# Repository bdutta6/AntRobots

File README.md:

# ant-robots

##Contributors

Initial Author: Vadim Linevich
Email: vadim.linevich@gmail.com

Modified by: Jungsoo Park
Email : ryanryan0906@hotmail.com

Modified by: Bahnisikha Dutta
Email : bahnisikha3474@gmail.com

Modified by: Ross Warkentin
Email: ross.warkentin@gmail.com

[Guide to .md files](https://guides.github.com/features/mastering-markdown/)

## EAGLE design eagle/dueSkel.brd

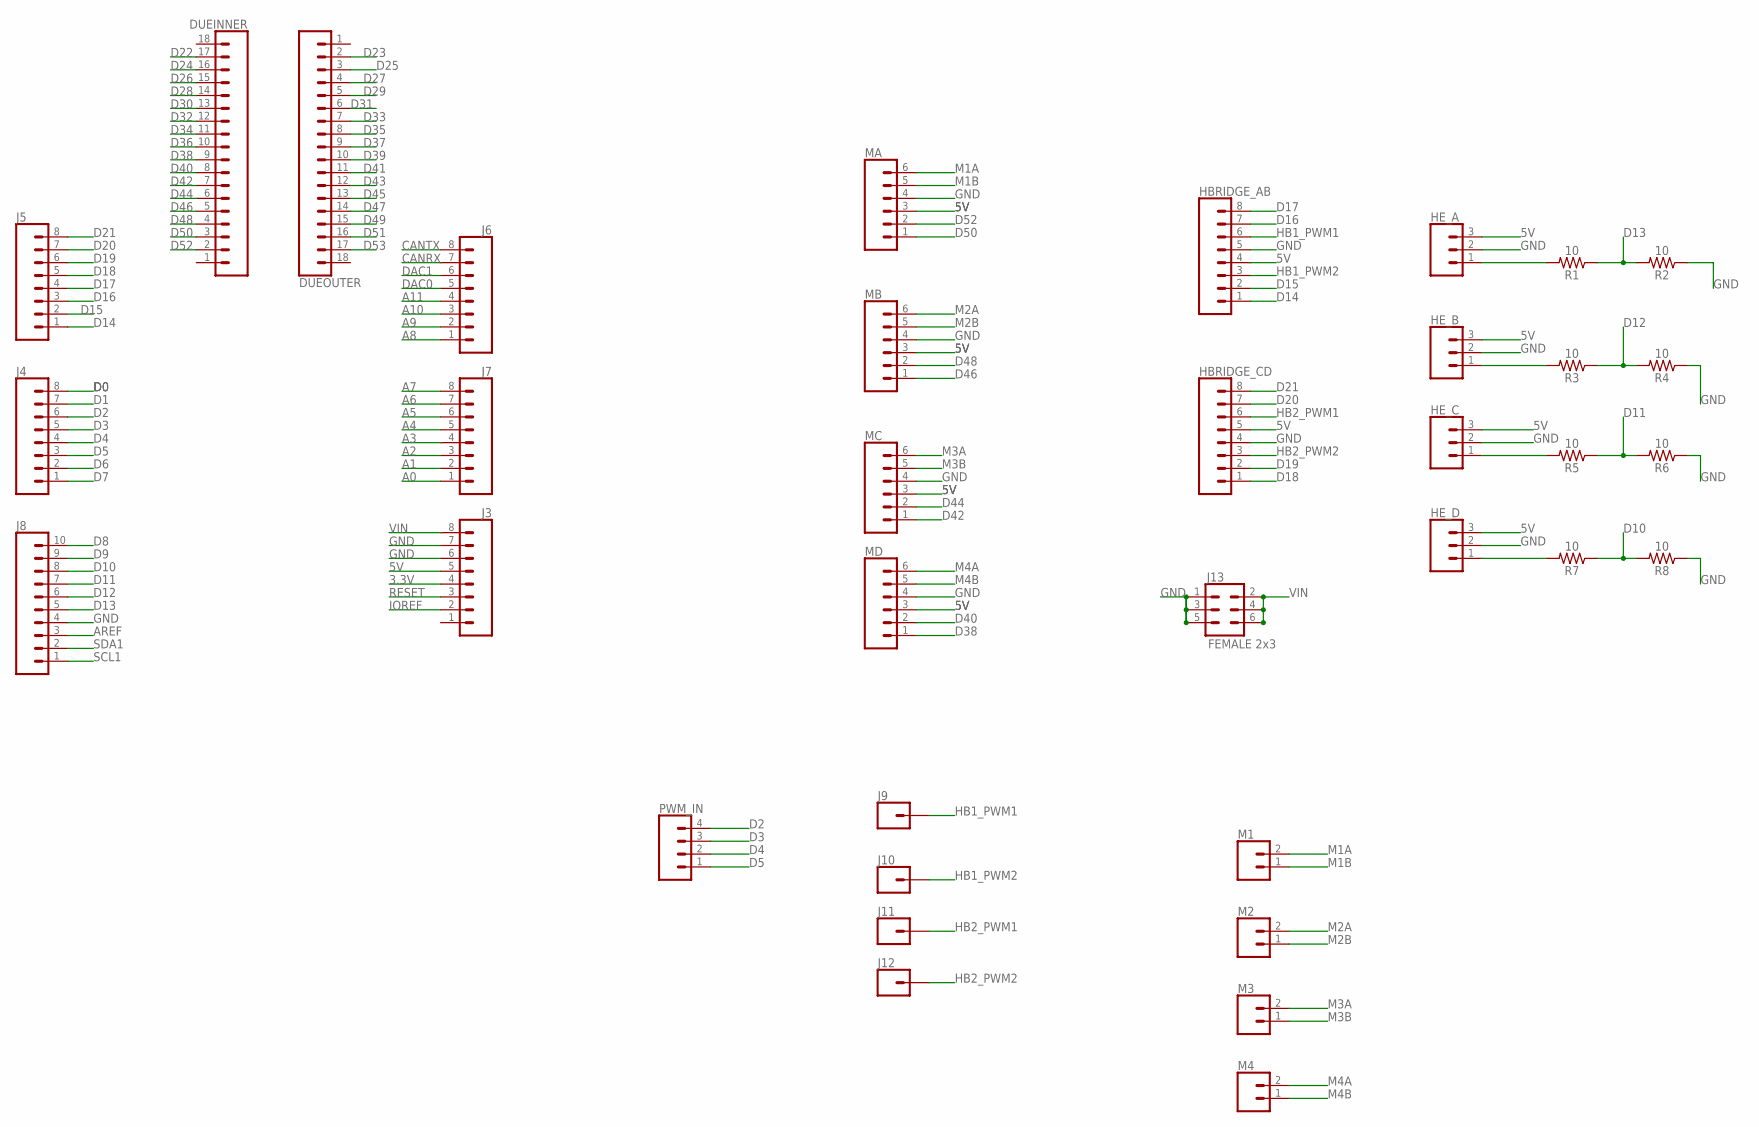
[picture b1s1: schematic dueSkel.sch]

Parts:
DUEINNER: CONN_18; 1X18
DUEOUTER: CONN_18; 1X18
HBRIDGE_AB: CONN_08"; 1X08
HBRIDGE_CD: CONN_08"; 1X08
HE_A: CONN_03; 1X03
HE_B: CONN_03; 1X03
HE_C: CONN_03; 1X03
HE_D: CONN_03; 1X03
J3, J4, J5, J6, J7: CONN_08"; 1X08
J8: CONN_10"; 1X10
J9, J10, J11, J12: CONN_01; 1X01
J13: FEMALE 2x3; 2X3
M1, M2, M3, M4: CONN_02; 1X02
MA: CONN_06SILK_FEMALE_PTH; 1X06
MB: CONN_06SILK_FEMALE_PTH; 1X06
MC: CONN_06SILK_FEMALE_PTH; 1X06
MD: CONN_06SILK_FEMALE_PTH; 1X06
PWM_IN: CONN_04; 1X04
R1, R2, R3, R4, R5, R6, R7, R8: 10; AXIAL-0.3

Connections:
3.3V: J3.4
5V: HBRIDGE_AB.4, HBRIDGE_CD.5, HE_A.3, HE_B.3, HE_C.3, HE_D.3, J3.5, MA.3, MB.3, MC.3, MD.3
A0: J7.1
A1: J7.2
A2: J7.3
A3: J7.4
A4: J7.5
A5: J7.6
A6: J7.7
A7: J7.8
A8: J6.1
A9: J6.2
A10: J6.3
A11: J6.4
AREF: J8.3
CANRX: J6.7
CANTX: J6.8
D0: J4.8
D1: J4.7
D2: J4.6, PWM_IN.4
D3: J4.5, PWM_IN.3
D4: J4.4, PWM_IN.2
D5: J4.3, PWM_IN.1
D6: J4.2
D7: J4.1
D8: J8.10
D9: J8.9
D10: J8.8, R7.P$1 (1), R8.P$2 (2)
D11: J8.7, R5.P$1 (1), R6.P$2 (2)
D12: J8.6, R3.P$1 (1), R4.P$2 (2)
D13: J8.5, R1.P$1 (1), R2.P$2 (2)
D14: HBRIDGE_AB.1, J5.1
D15: HBRIDGE_AB.2, J5.2
D16: HBRIDGE_AB.7, J5.3
D17: HBRIDGE_AB.8, J5.4
D18: HBRIDGE_CD.1, J5.5
D19: HBRIDGE_CD.2, J5.6
D20: HBRIDGE_CD.7, J5.7
D21: HBRIDGE_CD.8, J5.8
D22: DUEINNER.17
D23: DUEOUTER.2
D24: DUEINNER.16
D25: DUEOUTER.3
D26: DUEINNER.15
D27: DUEOUTER.4
D28: DUEINNER.14
D29: DUEOUTER.5
D30: DUEINNER.13
D31: DUEOUTER.6
D32: DUEINNER.12
D33: DUEOUTER.7
D34: DUEINNER.11
D35: DUEOUTER.8
D36: DUEINNER.10
D37: DUEOUTER.9
D38: DUEINNER.9, MD.1
D39: DUEOUTER.10
D40: DUEINNER.8, MD.2
D41: DUEOUTER.11
D42: DUEINNER.7, MC.1
D43: DUEOUTER.12
D44: DUEINNER.6, MC.2
D45: DUEOUTER.13
D46: DUEINNER.5, MB.1
D47: DUEOUTER.14
D48: DUEINNER.4, MB.2
D49: DUEOUTER.15
D50: DUEINNER.3, MA.1
D51: DUEOUTER.16
D52: DUEINNER.2, MA.2
D53: DUEOUTER.17
DAC0: J6.5
DAC1: J6.6
GND: HBRIDGE_AB.5, HBRIDGE_CD.4, HE_A.2, HE_B.2, HE_C.2, HE_D.2, J3.6, J3.7, J8.4, J13.1, J13.3, J13.5, MA.4, MB.4, MC.4, MD.4, R2.P$1 (1), R4.P$1 (1), R6.P$1 (1), R8.P$1 (1)
HB1_PWM1: HBRIDGE_AB.6, J9.1
HB1_PWM2: HBRIDGE_AB.3, J10.1
HB2_PWM1: HBRIDGE_CD.6, J11.1
HB2_PWM2: HBRIDGE_CD.3, J12.1
IOREF: J3.2
M1A: M1.2, MA.6
M1B: M1.1, MA.5
M2A: M2.2, MB.6
M2B: M2.1, MB.5
M3A: M3.2, MC.6
M3B: M3.1, MC.5
M4A: M4.2, MD.6
M4B: M4.1, MD.5
unnamed: HE_A.1, R1.P$2 (2)
unnamed: HE_B.1, R3.P$2 (2)
unnamed: HE_C.1, R5.P$2 (2)
unnamed: HE_D.1, R7.P$2 (2)
RESET: J3.3
SCL1: J8.1
SDA1: J8.2
VIN: J3.8, J13.2, J13.4, J13.6

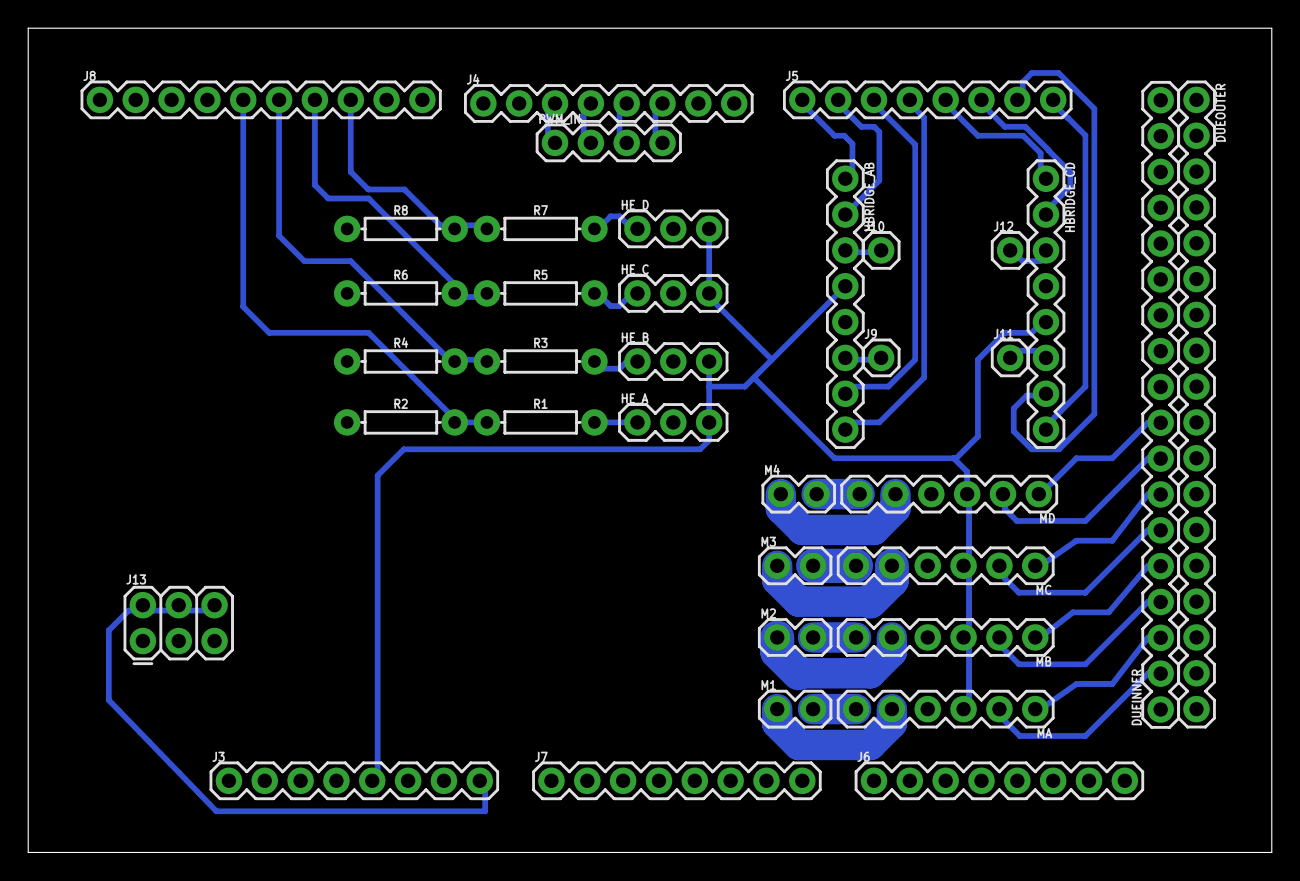
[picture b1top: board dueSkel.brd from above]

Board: 2 copper layers, 88.1 x 58.4 mm, 36 parts (0 on the bottom side), 43 nets.

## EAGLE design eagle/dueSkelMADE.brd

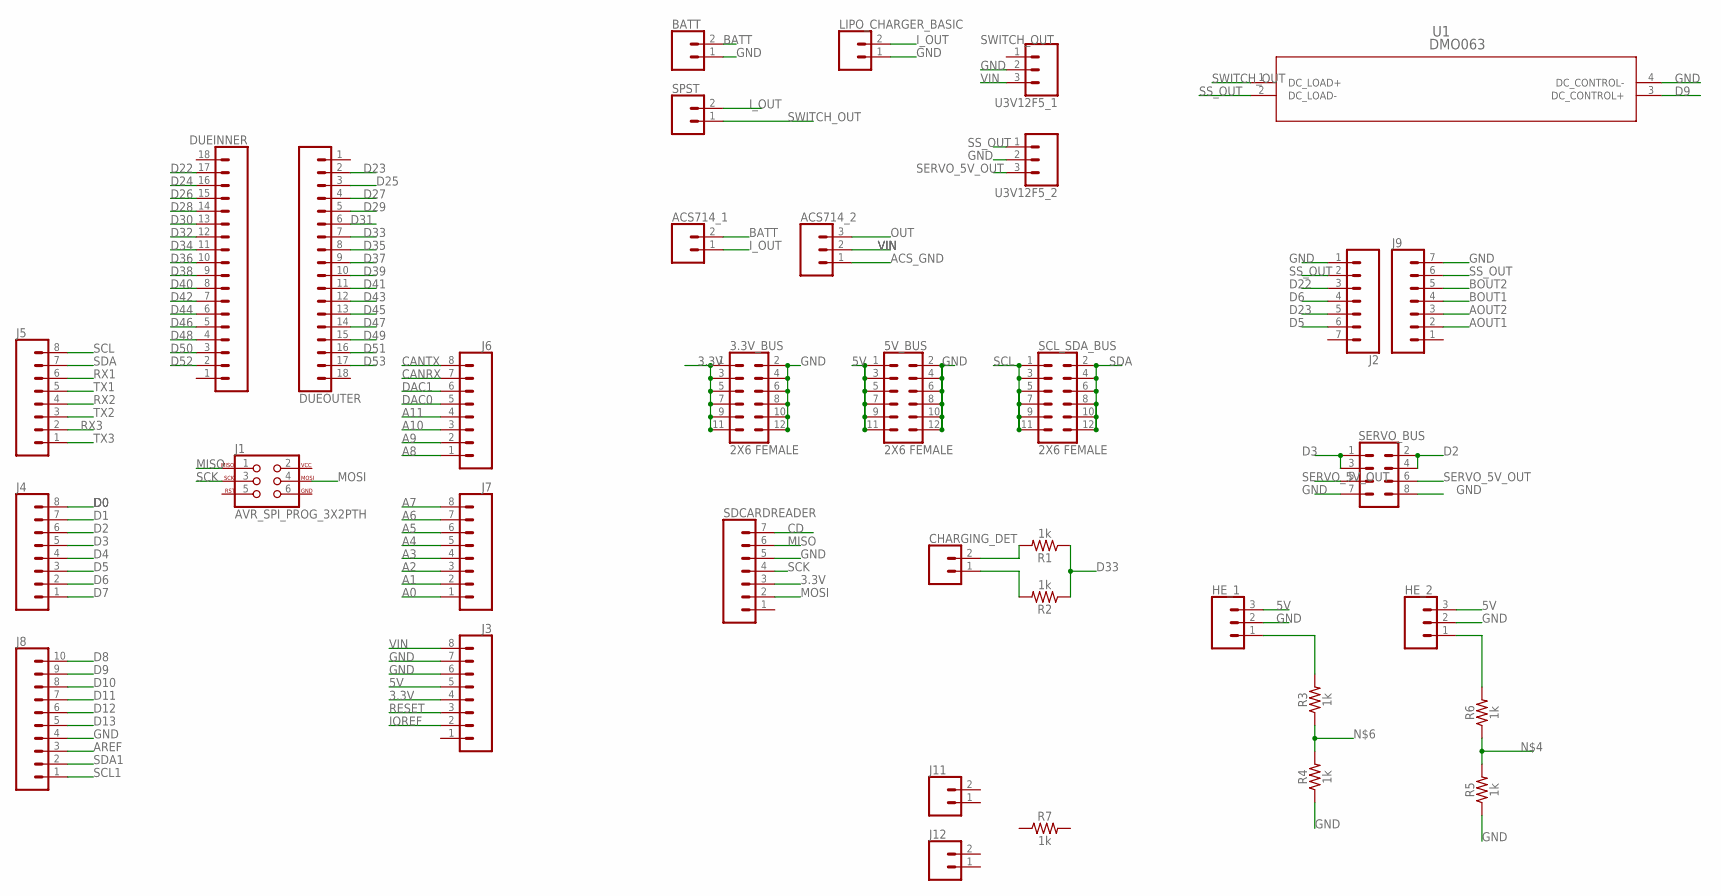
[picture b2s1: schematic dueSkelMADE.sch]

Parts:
3.3V_BUS, 5V_BUS: 2X6 FEMALE; 2X6
ACS714_1: CONN_02; 1X02
ACS714_2: CONN_03; 1X03
BATT: CONN_02; 1X02
CHARGING_DET: CONN_02; 1X02
DUEINNER: CONN_18; 1X18
DUEOUTER: CONN_18; 1X18
HE_1, HE_2: CONN_03; 1X03
J1: AVR_SPI_PROG_3X2PTH; 2X3
J2, J9: CONN_07; 1X07
J3, J4, J5, J6, J7: CONN_08"; 1X08
J8: CONN_10"; 1X10
J11, J12: CONN_02; 1X02
LIPO_CHARGER_BASIC: CONN_02; 1X02
R1, R2, R3, R4, R5, R6, R7: 1k; AXIAL-0.3
SCL_SDA_BUS: 2X6 FEMALE; 2X6
SDCARDREADER: CONN_07; 1X07
SERVO_BUS: CONN_04X2; 2X4
SPST: CONN_02; 1X02
U1: DMO063; SIP-4_DMO
U3V12F5_1, U3V12F5_2: CONN_03; 1X03

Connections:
3.3V: 3.3V_BUS.1, 3.3V_BUS.3, 3.3V_BUS.5, 3.3V_BUS.7, 3.3V_BUS.9, 3.3V_BUS.11, J3.4, SDCARDREADER.3
5V: 5V_BUS.1, 5V_BUS.3, 5V_BUS.5, 5V_BUS.7, 5V_BUS.9, 5V_BUS.11, HE_1.3, HE_2.3, J3.5
A0: J7.1
A1: J7.2
A2: J7.3
A3: J7.4
A4: J7.5
A5: J7.6
A6: J7.7
A7: J7.8
A8: J6.1
A9: J6.2
A10: J6.3
A11: J6.4
ACS_GND: ACS714_2.1
AOUT1: J9.2
AOUT2: J9.3
AREF: J8.3
BATT: ACS714_1.2, BATT.2
BOUT1: J9.4
BOUT2: J9.5
CANRX: J6.7
CANTX: J6.8
CD: SDCARDREADER.7
D0: J4.8
D1: J4.7
D2: J4.6, SERVO_BUS.2, SERVO_BUS.4
D3: J4.5, SERVO_BUS.1, SERVO_BUS.3
D4: J4.4
D5: J2.6, J4.3
D6: J2.4, J4.2
D7: J4.1
D8: J8.10
D9: J8.9, U1.3 (DC_CONTROL+)
D10: J8.8
D11: J8.7
D12: J8.6
D13: J8.5
D22: DUEINNER.17, J2.3
D23: DUEOUTER.2, J2.5
D24: DUEINNER.16
D25: DUEOUTER.3
D26: DUEINNER.15
D27: DUEOUTER.4
D28: DUEINNER.14
D29: DUEOUTER.5
D30: DUEINNER.13
D31: DUEOUTER.6
D32: DUEINNER.12
D33: DUEOUTER.7, R1.P$1 (1), R2.P$1 (1)
D34: DUEINNER.11
D35: DUEOUTER.8
D36: DUEINNER.10
D37: DUEOUTER.9
D38: DUEINNER.9
D39: DUEOUTER.10
D40: DUEINNER.8
D41: DUEOUTER.11
D42: DUEINNER.7
D43: DUEOUTER.12
D44: DUEINNER.6
D45: DUEOUTER.13
D46: DUEINNER.5
D47: DUEOUTER.14
D48: DUEINNER.4
D49: DUEOUTER.15
D50: DUEINNER.3
D51: DUEOUTER.16
D52: DUEINNER.2
D53: DUEOUTER.17
DAC0: J6.5
DAC1: J6.6
GND: 3.3V_BUS.2, 3.3V_BUS.4, 3.3V_BUS.6, 3.3V_BUS.8, 3.3V_BUS.10, 3.3V_BUS.12, 5V_BUS.2, 5V_BUS.4, 5V_BUS.6, 5V_BUS.8, 5V_BUS.10, 5V_BUS.12, BATT.1, HE_1.2, HE_2.2, J2.1, J3.6, J3.7, J8.4, J9.7, LIPO_CHARGER_BASIC.1, R4.P$1 (1), R5.P$1 (1), SDCARDREADER.5, SERVO_BUS.7, SERVO_BUS.8, U1.4 (DC_CONTROL-), U3V12F5_1.2, U3V12F5_2.2
IOREF: J3.2
I_OUT: ACS714_1.1, LIPO_CHARGER_BASIC.2, SPST.2
MISO: J1.1, SDCARDREADER.6
MOSI: J1.4, SDCARDREADER.2
unnamed: CHARGING_DET.1, R2.P$2 (2)
unnamed: CHARGING_DET.2, R1.P$2 (2)
unnamed: HE_2.1, R6.P$2 (2)
unnamed: R5.P$2 (2), R6.P$1 (1)
unnamed: HE_1.1, R3.P$2 (2)
unnamed: R3.P$1 (1), R4.P$2 (2)
OUT: ACS714_2.3
RESET: J3.3
RX1: J5.6
RX2: J5.4
RX3: J5.2
SCK: J1.3, SDCARDREADER.4
SCL: J5.8, SCL_SDA_BUS.1, SCL_SDA_BUS.3, SCL_SDA_BUS.5, SCL_SDA_BUS.7, SCL_SDA_BUS.9, SCL_SDA_BUS.11
SCL1: J8.1
SDA: J5.7, SCL_SDA_BUS.2, SCL_SDA_BUS.4, SCL_SDA_BUS.6, SCL_SDA_BUS.8, SCL_SDA_BUS.10, SCL_SDA_BUS.12
SDA1: J8.2
SERVO_5V_OUT: SERVO_BUS.5, SERVO_BUS.6, U3V12F5_2.3
SS_OUT: J2.2, J9.6, U1.2 (DC_LOAD-), U3V12F5_2.1
SWITCH_OUT: SPST.1, U1.1 (DC_LOAD+)
TX1: J5.5
TX2: J5.3
TX3: J5.1
VIN: ACS714_2.2, J3.8, U3V12F5_1.3

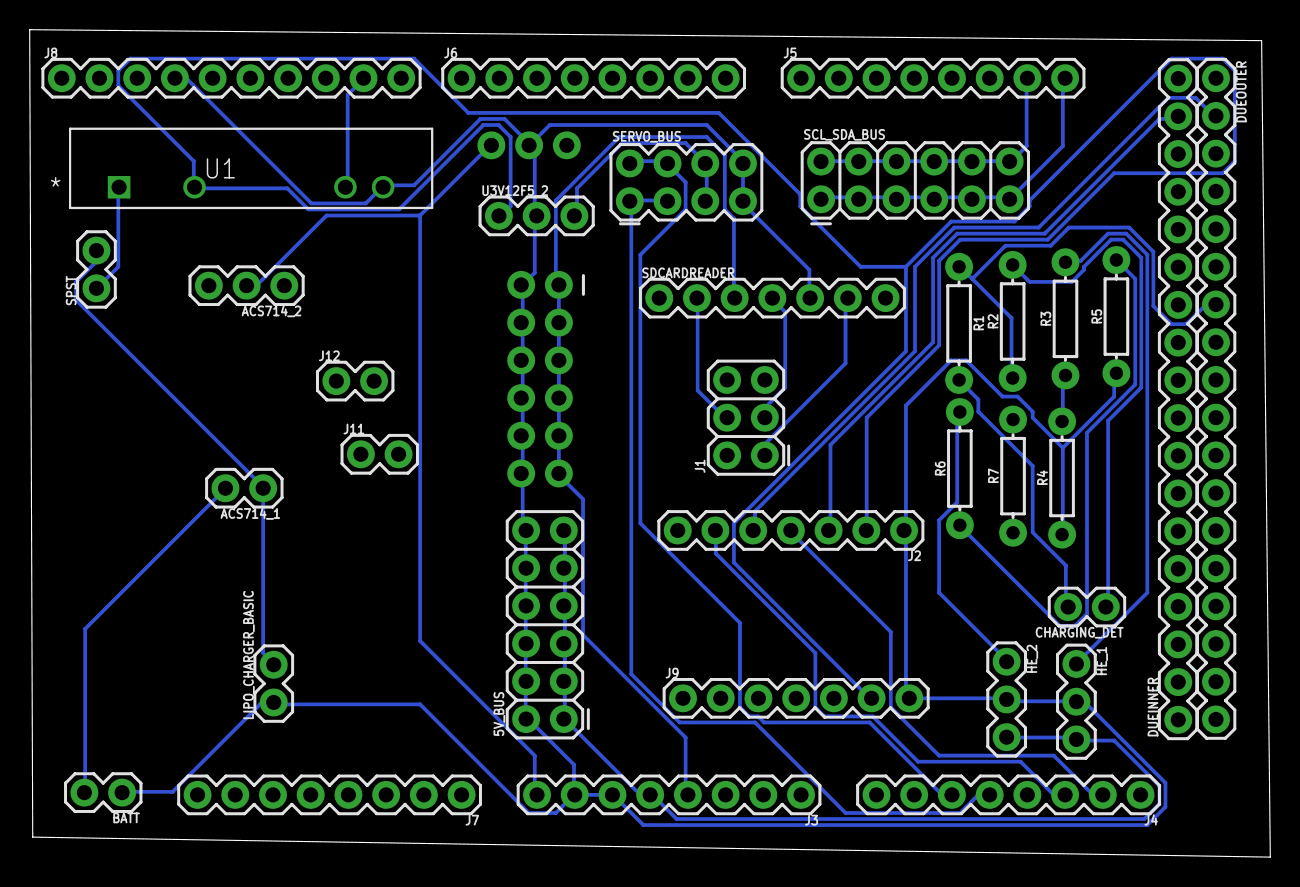
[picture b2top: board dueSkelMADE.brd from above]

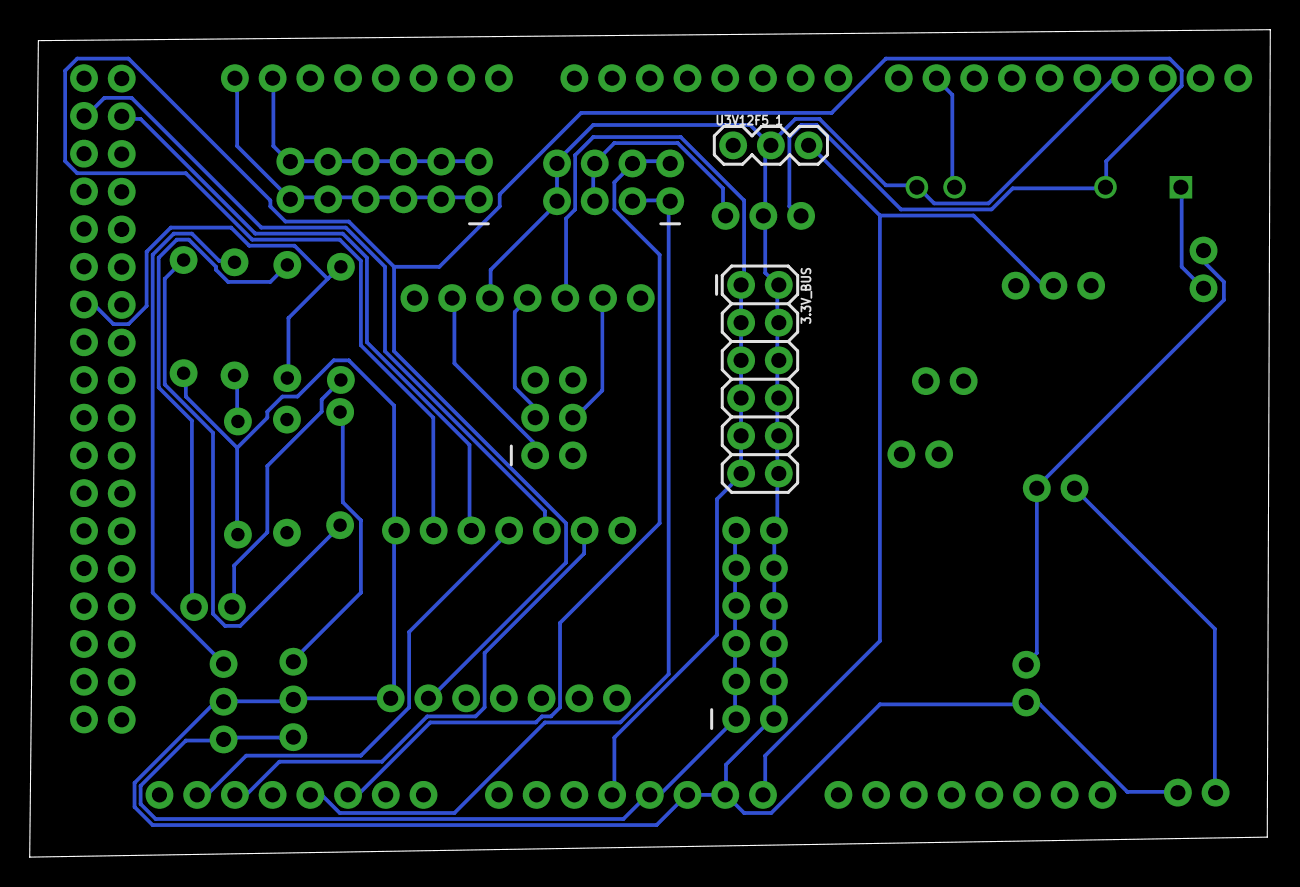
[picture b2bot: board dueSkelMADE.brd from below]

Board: 2 copper layers, 83.5 x 55.7 mm, 36 parts (2 on the bottom side), 28 nets.

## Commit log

2016-10-12 Initializing all of the codebase
2016-10-12 rearranging things
2016-10-13 testing ui commits
2016-10-13 test test
2016-10-13 am i in the test branch now?
2016-10-13 master edit
2016-10-13 fixing a line error?
2016-10-14 Mostly formatting
2016-10-14 Commut changes in due
2016-10-14 testing_branch personal
2016-10-14 Comments for TEST_SWITCHES and TEST_CAP
2016-10-14 Several Updates
    Began migrating test-related code to TestVals.h file -- cpp file in the
    future? It would be good to pull all of the test methods out of the main
    .ino file. Also created a part documentation folder for storing
    documentation related to the hardware.
2016-10-14 Several Updates #2
    Messed up last commit
2016-10-14 Fix readme
2016-10-14 Moved testing values into the RobotSelector file to that there is only one file to edit to set up a run/test
2016-10-14 Syntax and testing
    I made the testing methods for the capacitors a little bit easier to
    execute in the fio_wireless method, and tidied up a lot of stuff as I
    read through the code.
2016-10-17 Parts documentation
2016-10-17 Modified testing approach
    Now adding a new test is as simple as adding a test state to the global
    enumeration and adding a test method to the switch-case implementation.
    Can capture the flow-control with an infinite loop for simply print a
    statement to Serial.
2016-10-17 TEST_DRIVE_MOTORS
    Testing that the motors on the robots which do not move have operational
    motors. They do, so there must be something off with their controller,
    or the control flow of goingInMode. Perhaps in FollowLane (meaning they
    have a bad pixy or PD parameters)
2016-10-18 Testing with TEST_TURN_HEADING
2016-10-19 TurnHeadingRoss
    Created a new TurnHeading method to start from scratch and just get the
    simplest functionality. Works well, as long as the magnetometer is
    working. If the robot starts spinning, try resetting it. This is a
    hardware issue I think I found a solution for, but Bahni would be a
    better judge of that.
2016-10-20 Digging into drive, vision, and digging methods
2016-10-21 Cleaning up code as I review it.
    Trying to find possibe errors in control flow for turnheading
2016-10-21 More IMU testing
    I have found that I can intentionally hang the IMU, but I have not found
    a way to unhang it when it is not connected to USB
2016-10-21 more testing
2016-10-24 TurnHeadingRoss is working
    Need to work on ExitTunnel, GoingOut, and HandleContacts nows...
2016-10-24 TurnHeadingRoss is working
2016-10-25 I think the real problem is the connection from the IMU to the circuitry
    Add extensions and retest tomorrow. Things are looking better!
2016-10-27 Lots of work on the pixycam stuff.
    Accidentally updated the firmware on Bravo's pixycam and wiped the
    parameter settings. I found the .prm files in Desktop/antrobots_2.0 and
    loaded the roboJSP.prm onto it and it started working. Lots of things
    about the .prm file go against the online documentation, but it works
    so...yay.
2016-10-27 how it all started
2016-10-29 Added mpr121 capacitive sensor datasheet
2016-10-29 more mpr121 documentation
2016-10-30 upload #2
2016-10-30 testing - upload for running on personal machine
2016-10-31 all changes on. going to debug through personal and serial
2016-10-31 Found bug in checkHeadSensor()
2016-11-11 Mostly modifications I made while testing the power board issue. Still not resolved, but not as major of an issue for now.
2016-11-14 Made some modifications to goingout behavior. Just trying to keep things consistent between goingin and goingout
    Modified Kp for Alpha
    Modified goingin direction for Bravo
    Modified BASE_SPEED for Delta
2016-11-28 Tuning parameters in constants
2016-11-30 Adding doc
2016-11-30 rearrange
2016-12-01 December 1 Update
    Added some caster documentation
    Commented out unnecessary debugging prints
    Tuned IMU parameters
2016-12-02 Some doc stuff mostly
2016-12-02 December 2 Update
2016-12-06 Fixing some capacitive sensor stuff
2016-12-12 Capacitive sensor tuning
2016-12-14 capacitive sensor updates
2016-12-20 commit doc changes
2016-12-20 imu matlab code
2016-12-21 imu tuning
2016-12-21 More tuning stuff. Close to running things?
2016-12-21 lots of imu tuning stuff
2016-12-21 doc update
2017-01-02 tuned all robots
2017-01-03 Formatting stuff relevant to lorenz runs and some documentation stuff
2017-01-03 readme
2017-01-03 test
2017-01-03 Lorenz and Timeout Behavior
2017-01-05 Revert "test"
    This reverts commit 41127ea1b7ae32a671fcc228c774af34a5d35e2f.
2017-01-05 MATLAB code buff, Doc update, Parameter update
    Added a uselessRun parameter to control dumping behavior in the case of
    a useless run.
    Also commented out a lot of unused functions. Consider deleting them...
    Moved Lorenz code to the if(goingIn)-statement in the main loop, but I
    want to talk with Will before I commit to this change - pretty confident
    this is the way to go.
2017-01-05 turning contact delays into followlane periods
2017-01-07 More PID control stuff
    Also added some camera stuff back in for detecting the color green
2017-01-08 Updated goingOut implementation and tuned caps
2017-01-16 01/16 Week updates
    moved lorenz/reversal stuff to robot selector so all trial stuff can be
    set from the RobotSelector.h file,
    Added a Charger testing method.
    Wrote a determineState method to allwo the robots to find where they
    were in the digging state machine prior to being turned on/reset.
    Changed the minimum threshold needed for the MAG3110 sensor. Probably
2017-01-18 01/17 commit
2017-01-31 Fio no longer resets
2017-02-06 Lots of updates
    I think it may be possible to remove the Fio from the robots altogether,
    but in order to do this I need to demonstrate that the Due can perform
    all of the tasks on the available pins.
    I wrote the hardSerLCD library, so that the Due can now write to the LCD
    screen on any of the open TX lines.
    I also included the .pptx Vadim wrote for starting the robots in the
2017-02-17 Transitioning away from the Fio
2017-03-21 New robot prototyping
2017-05-19 Addedcode for new platform
2017-05-19 Changed forward to backward
    Testing reverse behavior
2017-05-26 made to grab particles and drop them off
    Moves forward with gripper down, picks up material, raises gripper, backs out, drops off the particles, moves forward a bit, drops gripper, then repeats
2017-05-27 Control all 4 motors individually
    adjusted code to allow for all 4 motors to be controlled
2017-05-27 Added suppporting library code to the quad folder
    Intention is to implement PID control using the Pixycam
2017-05-27 Deleted things
2017-05-27 Fixed commit-merge issues
2017-05-27 Getting supporting vision files up in quad
2017-05-27 Pixy Cam stuff included
2017-05-27 documentation
2017-05-27 FollowLane() included
    needs to be worked on in detail
2017-05-27 serial print stuff
2017-05-29 Got the PID controller working for the PixyCam
2017-06-01 Lots of changes
    Reorganized the codebase. Deprecated files from Mk2 are now in the
    deprecated directory. New codebase is all together in due_digger_mk3
    with all of the supporting code that is needed. Note that it currently
    does not compile: still need to track down the relay and charger issues.
    I think that it is just a pin assignment issue in either the def*.h or
    the constants*.h files for A, but I could be wrong.
2017-06-02 Updating def*.h files to reflect new motor methods
2017-06-02 test for wheels
    checked how the new wheels were working without pixy cam input
2017-06-02 testing magnetometer
    changed TEST_CASE to TEST_MAG
2017-06-05 testing magnetometer
2017-06-07 commented out some errors
2017-06-07 Updating calibration files
2017-06-07 Magnetometer testing and electrical documentation
2017-06-07 Debugging behaviors
2017-06-07 Solved motor communication issues
2017-06-07 try again?
2017-06-08 Docs
2017-06-09 LCD?
2017-06-09 testing out drive motors and current
2017-06-09 Updating docts and old robot parameters
2017-06-10 test power method included and lcd fixed
2017-06-12 forward methods moved to motorboard
2017-06-12 moved drive methods to motorboard
    except for Forward, Backward, Right, and Left
2017-06-12 Added new base speeds for turns
    when turning, robot required the motors to turn at increased speeds which are represented by LEFT_BASE_SPEED and RIGHT_BASE_SPEED
2017-06-14 Added electrical doc for daniel
2017-06-14 debugging things on line follower
2017-06-18 Just some docs
2017-06-19 line follower code
2017-06-21 commented for clarification
2017-06-21 PID line follower code
    modified code given online to work for line follower bot. either need more sensors added in order to properly trace the line or need to play with the Kd and Kp values
2017-06-24 PID control for a motor with encoder
    Code is for one motor and one encoder. probably needs tweaking on the constants
2017-06-26 fixed some calls in the code
    still needs some work on the constants in the PID control
2017-06-26 finished the PD control of the motor control
2017-06-27 Plotted all collected data from encoder
    Run plot_PID_motor_encoder to obtain plots of all the data.
2017-07-02 4 motors encoder data and program
2017-07-02 adusted time scale to be in seconds
2017-07-04 fix for changing motor speeds
    pretty sure this is a solution for changing motor speeds without dropping in set position
2017-07-06 Ran more tests and tuned gains
    the integral gain can be tuned to be greater than 0 if there's modifications to the PID code to counter "integral windup"
2017-07-06 Tests and plots of those tests
    ran a few tests where the slope of the ramp changed with respect to time and another set of tests where it changed with position. Also ran tests with different gains and plotted those to tune the val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
2017-07-07 Set up code to run all motors at 1 rpm
2017-07-08 images and documentation
2017-07-08 docs and testing
2017-07-09 Worked integral control in PID
    The encoder code has been made much more accurate with integral control. The constants can be fiddled with to make it even more accurate. The script "quick_plot_2" shows the final tests and "for_the_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
2017-07-10 modified constants for ramp testing
2017-07-12 newest version
2017-07-12 work on mk2
2017-07-12 Added Hall effect interrupts
2017-07-12 cleg class abstraction
2017-07-12 Finished implementing hall effect sensors in the code
2017-07-14 Newest code
2017-07-19 rearranged the files
2017-07-19 ross' stuff
2017-07-20 updated the gains
2017-07-21 pseudocode
2017-07-22 added homing method
2017-07-22 cleg boards
2017-07-23 docs for bahni
2017-08-21 Updated code for walking robot
2017-08-25 made the changing speeds a triangular wave instead of a square wave
2017-09-04 updated find_speed method and PID control
2017-10-09 Updated codes, arduino shields, and a new repositiory

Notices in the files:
parts and their libraries:
SparkFun-Connectors: Licensing: Creative Commons ShareAlike 4.0 International - https://creativecommons.org/licenses/by-sa/4.0
